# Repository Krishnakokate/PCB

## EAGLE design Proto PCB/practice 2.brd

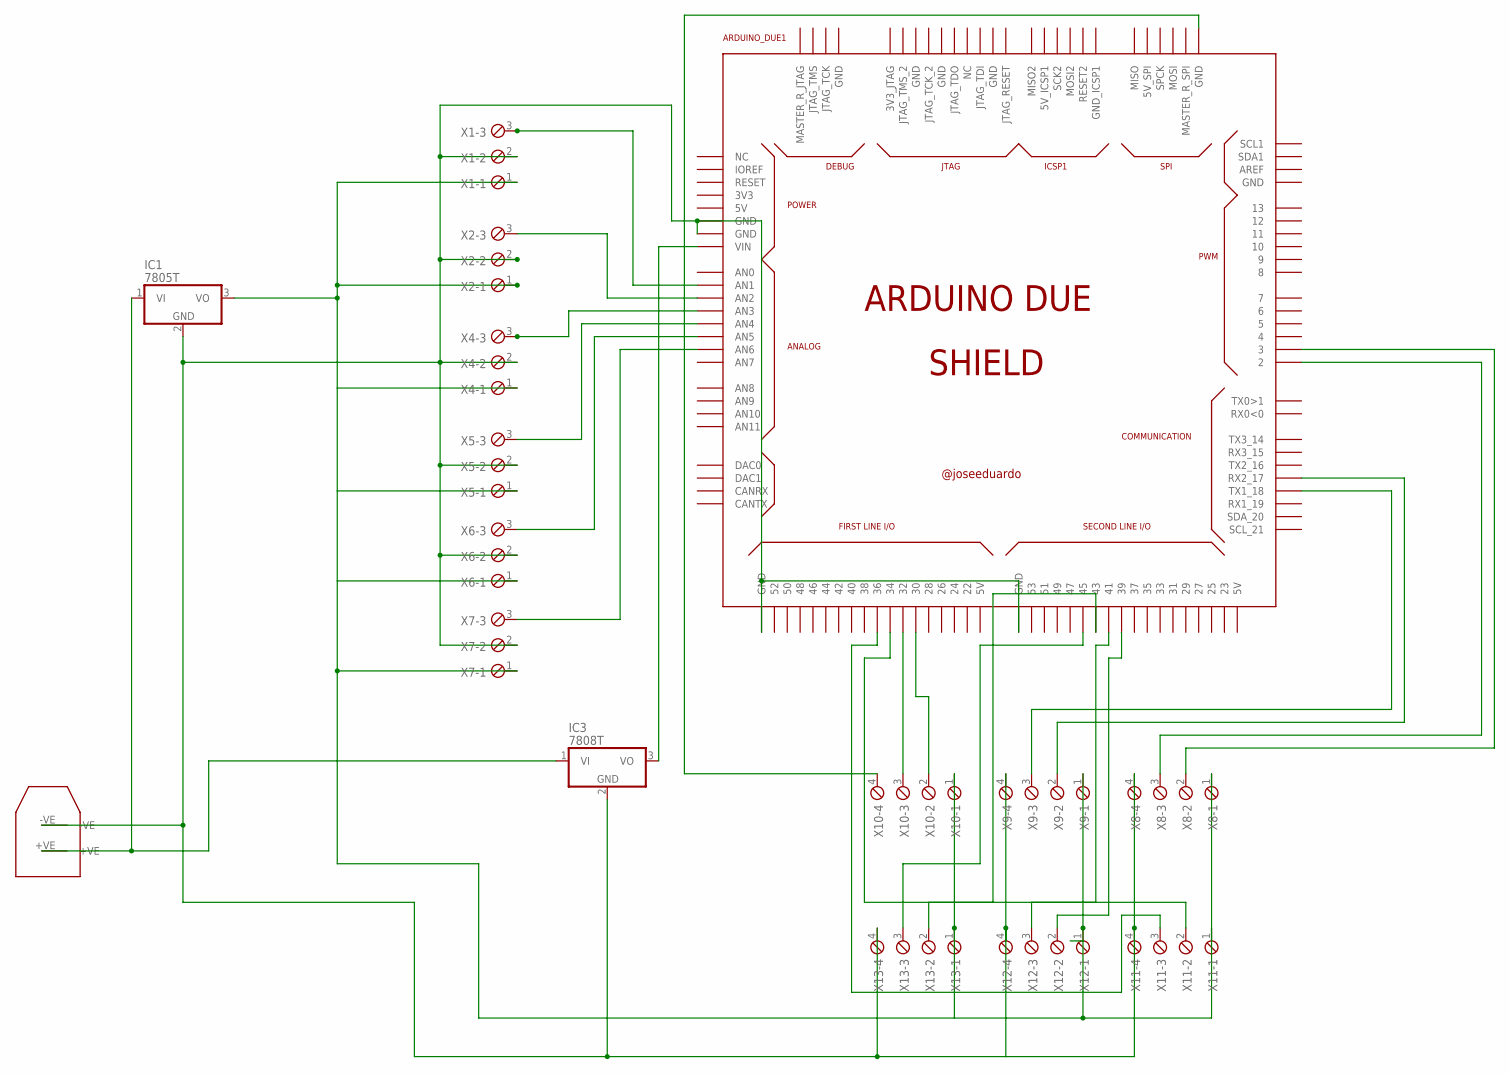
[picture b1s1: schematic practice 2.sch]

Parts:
ARDUINO_DUE1: ARDUINO_DUE_SHIELD
IC1: 7805T; TO220H
IC3: 7808T; TO220H
U$1: XT60XT60; XT60
X1, X2, X4, X5, X6, X7: MPT3; 3POL254
X8, X9, X10, X11, X12, X13: MPT4; 4POL254

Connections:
GND: ARDUINO_DUE1.GND, ARDUINO_DUE1.GND_1 (GND), ARDUINO_DUE1.GND_2 (GND), ARDUINO_DUE1.GND_3 (GND), IC1.2 (GND), IC3.2 (GND), U$1.-VE, X1.2, X2.2, X4.2, X5.2, X6.2, X7.2, X8.4, X9.4, X11.4, X12.4, X13.4
unnamed: ARDUINO_DUE1.36, X11.3
unnamed: ARDUINO_DUE1.A2 (AN2), X2.3
unnamed: ARDUINO_DUE1.A1 (AN1), X1.3
unnamed: ARDUINO_DUE1.GND_5 (GND), X10.4
unnamed: ARDUINO_DUE1.A3 (AN3), X4.3
unnamed: ARDUINO_DUE1.A4 (AN4), X5.3
unnamed: ARDUINO_DUE1.A5 (AN5), X6.3
unnamed: ARDUINO_DUE1.A6 (AN6), X7.3
unnamed: IC1.3 (VO), X1.1, X2.1, X4.1, X5.1, X6.1, X7.1, X8.1, X9.1, X10.1, X11.1, X12.1, X13.1
unnamed: ARDUINO_DUE1.30, X10.2
unnamed: ARDUINO_DUE1.32, X10.3
unnamed: IC1.1 (VI), IC3.1 (VI), U$1.+VE
unnamed: ARDUINO_DUE1.34, X11.2
unnamed: ARDUINO_DUE1.39, X12.2
unnamed: ARDUINO_DUE1.41, X12.3
unnamed: ARDUINO_DUE1.45, X13.3
unnamed: ARDUINO_DUE1.43, X13.2
unnamed: ARDUINO_DUE1.VIN, IC3.3 (VO)
unnamed: ARDUINO_DUE1.18 (TX1_18), X9.3
unnamed: ARDUINO_DUE1.17 (RX2_17), X9.2
unnamed: ARDUINO_DUE1.2, X8.3
unnamed: ARDUINO_DUE1.3, X8.2

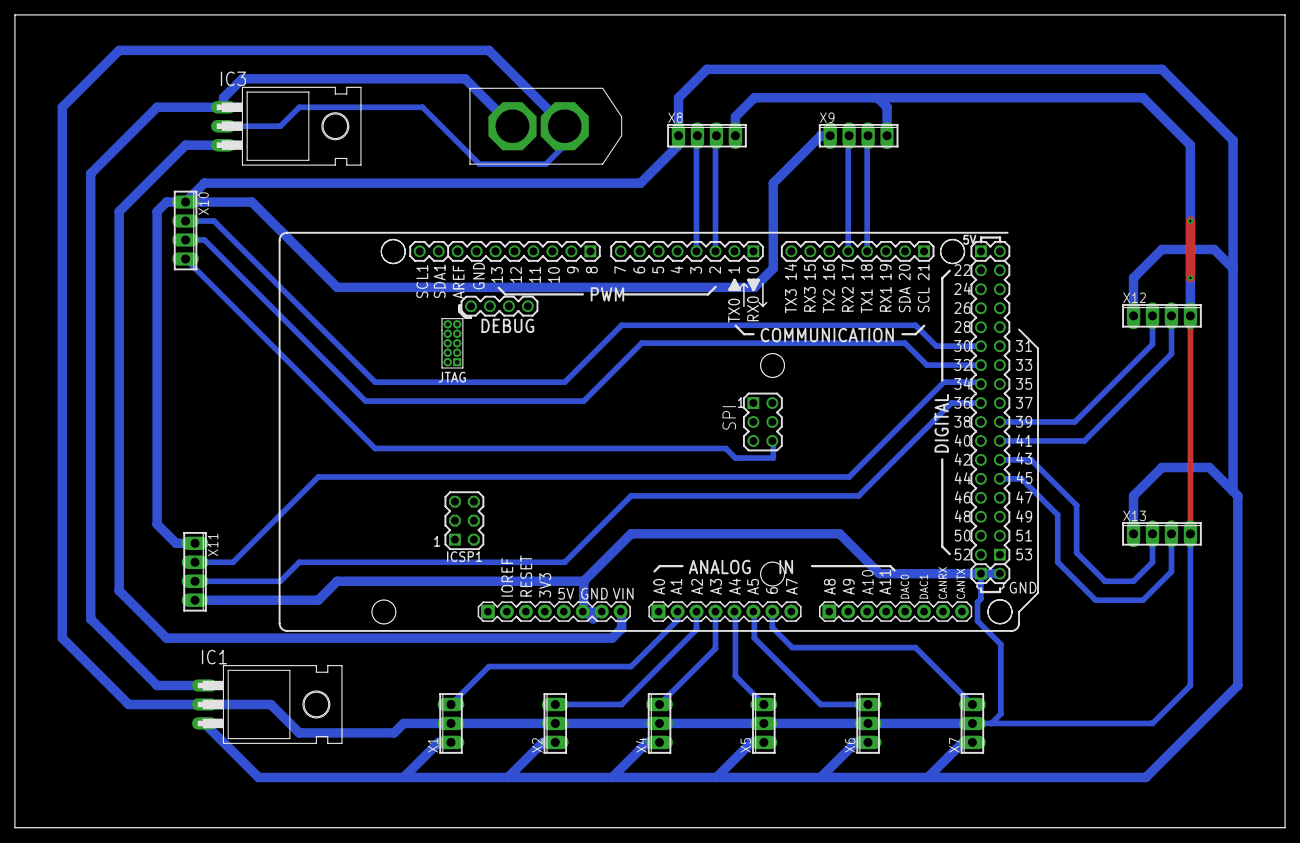
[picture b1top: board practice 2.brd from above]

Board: 2 copper layers, 170.2 x 108.9 mm, 16 parts (0 on the bottom side), 23 nets.

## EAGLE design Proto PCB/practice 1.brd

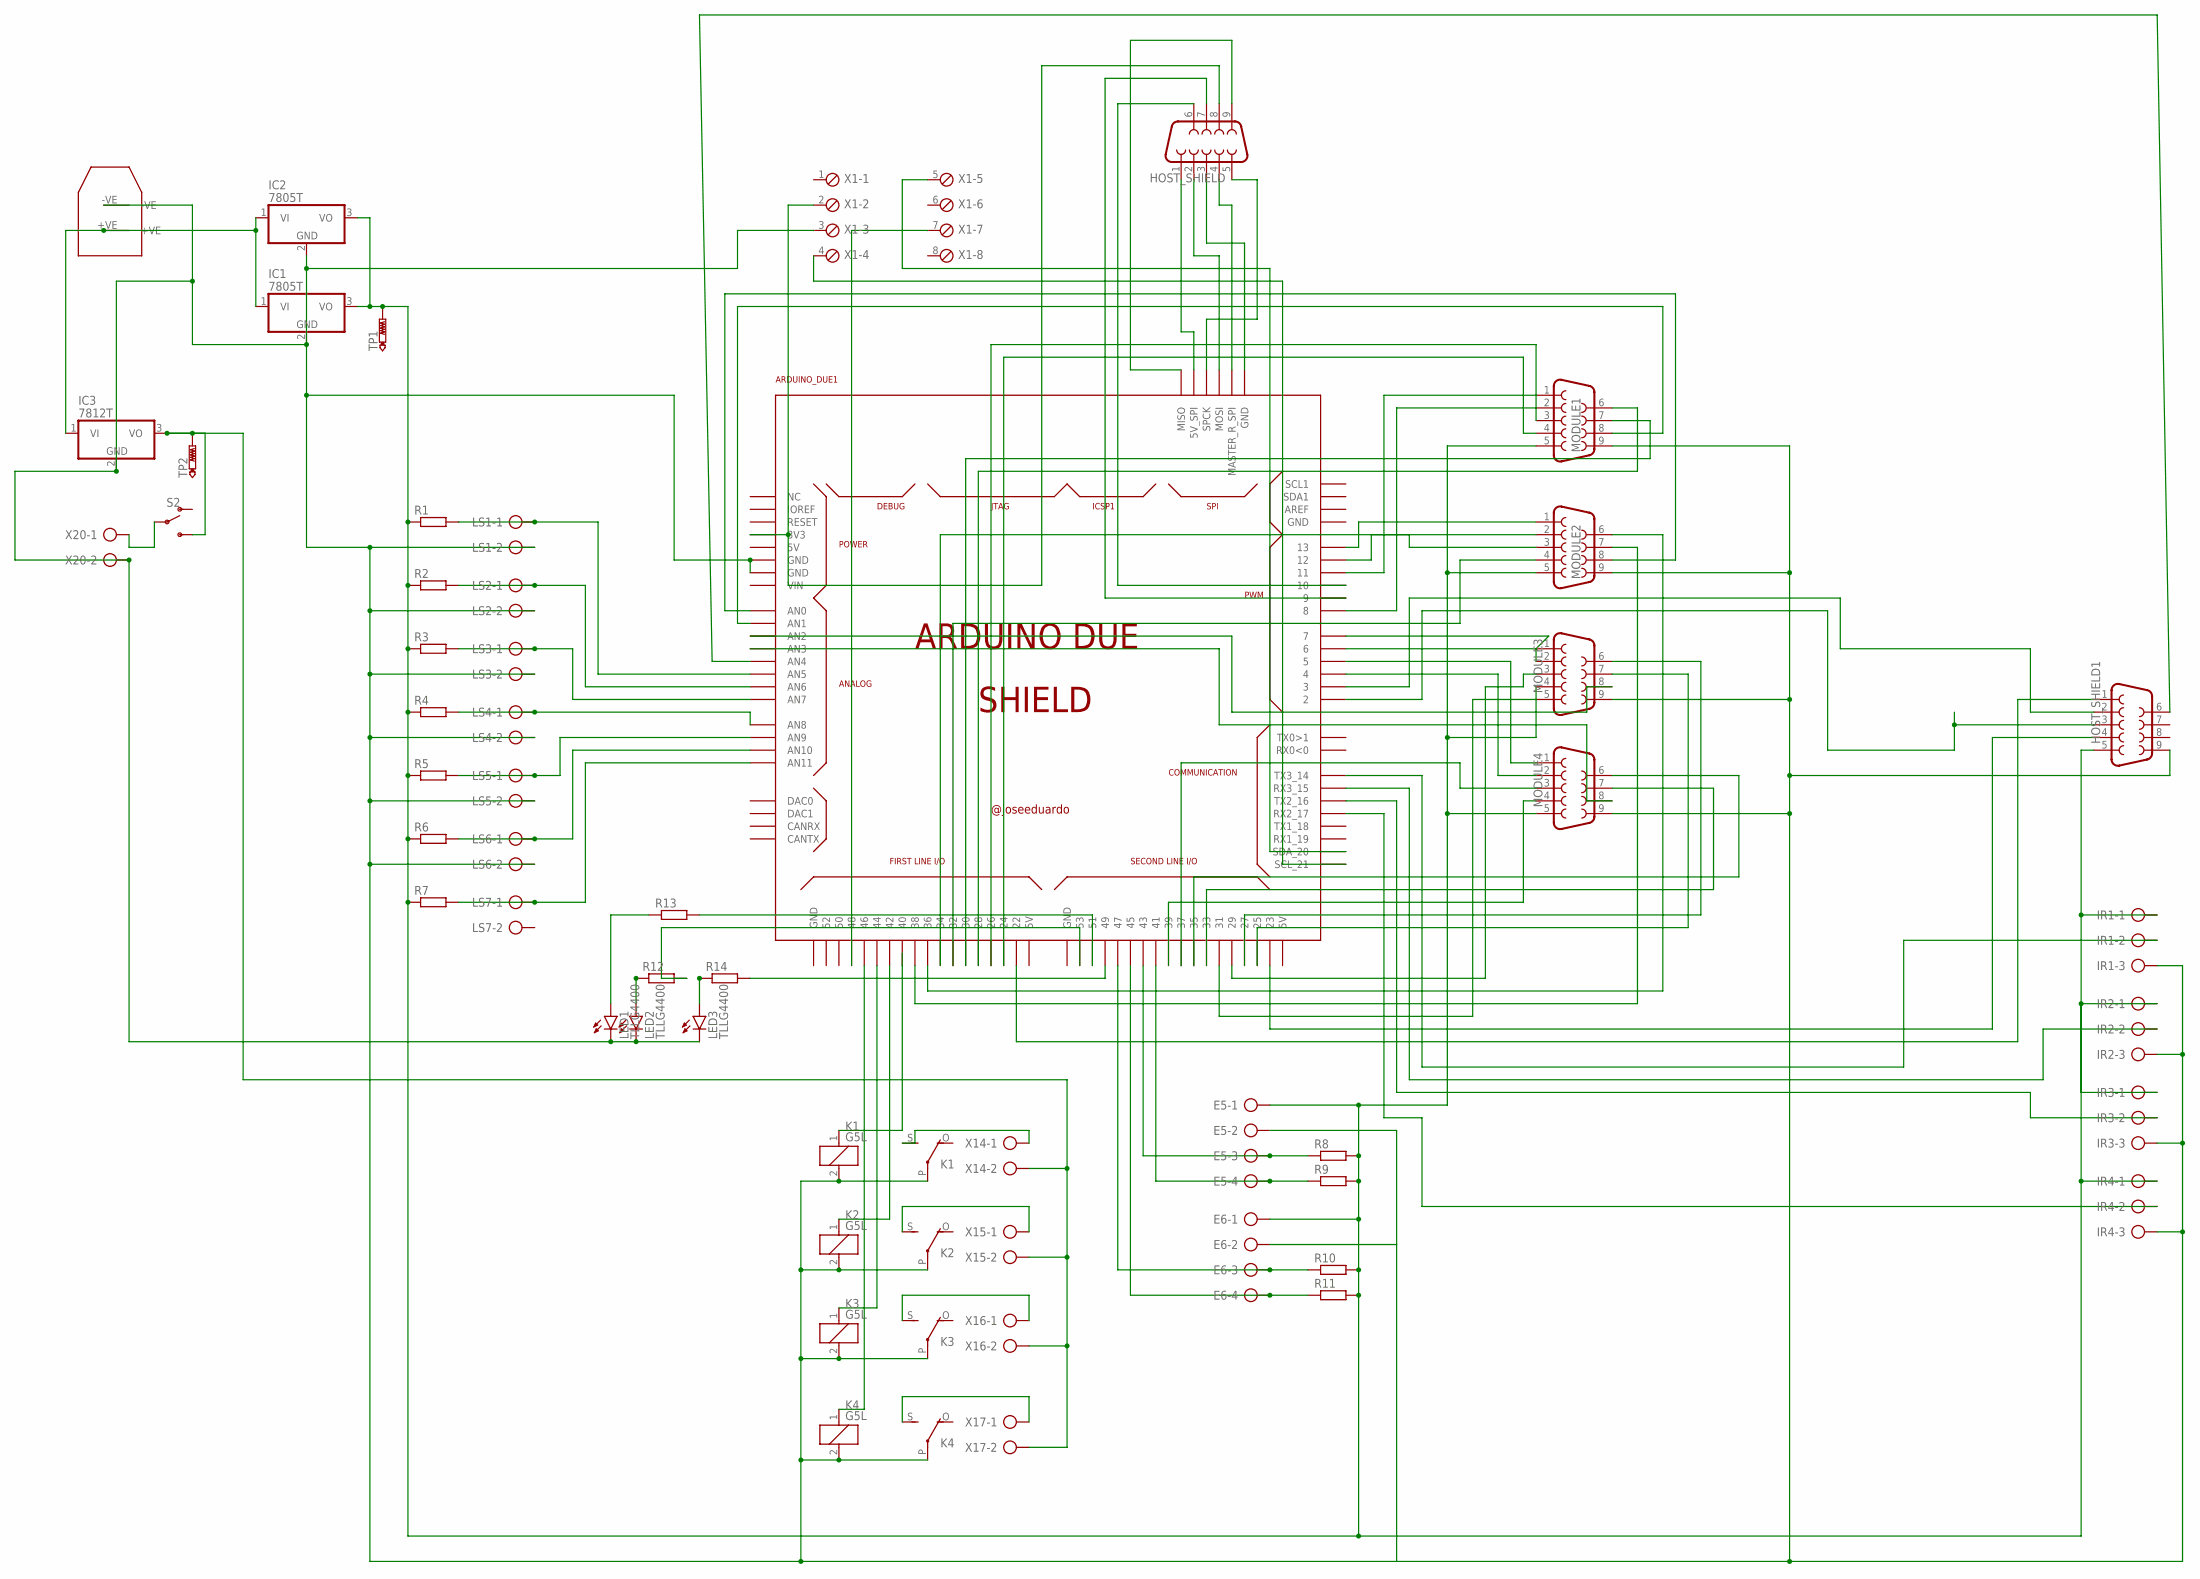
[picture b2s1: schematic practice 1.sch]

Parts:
ARDUINO_DUE1: ARDUINO_DUE_SHIELD
E5, E6: AK500/4-H
HOST_SHIELD, HOST_SHIELD1: DB9; DB9_MODULE
IC1, IC2: 7805T; TO220H
IC3: 7812T; TO220H
IR1, IR2, IR3, IR4: AK500/3-H
K1, K2, K3, K4: G5L; G5LE
LED1, LED2, LED3: TLLG4400; LED3MM
LS1, LS2, LS3, LS4, LS5, LS6, LS7: AK500/2-H
MODULE1, MODULE2, MODULE3, MODULE4: DB9; DB9_MODULE
R1, R2, R3, R4, R5, R6, R7, R8, R9, R10, R11, R12, R13, R14: R-EU_0309/10; 0309/10
S2: SWITCH-SPDT-PTH-11.6X4.0MM; SWITCH_SPDT_PTH_11.6X4.0MM
TP1, TP2: PTR1PAD1-13; P1-13
U$1: XT60XT60; XT60
X1: MPT8; 8POL254
X14, X15, X16, X17, X20: AK500/2-H

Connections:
GND: ARDUINO_DUE1.GND, ARDUINO_DUE1.GND_1 (GND), E5.2, E6.2, HOST_SHIELD1.9, IC1.2 (GND), IC2.2 (GND), IC3.2 (GND), IR1.3, IR2.3, IR3.3, IR4.3, K1.2, K1.P, K2.2, K2.P, K3.2, K3.P, K4.2, K4.P, LED1.K (C), LED2.K (C), LED3.K (C), LS1.2, LS2.2, LS3.2, LS4.2, LS5.2, LS6.2, MODULE1.9, MODULE2.9, MODULE3.9, MODULE4.9, U$1.-VE, X1.3, X20.2
unnamed: ARDUINO_DUE1.35, MODULE4.6
unnamed: ARDUINO_DUE1.37, MODULE4.3
unnamed: ARDUINO_DUE1.39, MODULE4.4
unnamed: ARDUINO_DUE1.A5 (AN5), LS1.1, R1.2
unnamed: ARDUINO_DUE1.A6 (AN6), LS2.1, R2.2
unnamed: ARDUINO_DUE1.A7 (AN7), LS3.1, R3.2
unnamed: ARDUINO_DUE1.A8 (AN8), LS4.1, R4.2
unnamed: ARDUINO_DUE1.A9 (AN9), LS5.1, R5.2
unnamed: ARDUINO_DUE1.A10 (AN10), LS6.1, R6.2
unnamed: ARDUINO_DUE1.A11 (AN11), LS7.1, R7.2
unnamed: ARDUINO_DUE1.3, HOST_SHIELD1.2
unnamed: ARDUINO_DUE1.43, E5.3, R8.1
unnamed: ARDUINO_DUE1.A4 (AN4), HOST_SHIELD1.6
unnamed: ARDUINO_DUE1.40, K1.1
unnamed: ARDUINO_DUE1.41, E5.4, R9.1
unnamed: ARDUINO_DUE1.47, E6.3, R10.1
unnamed: ARDUINO_DUE1.45, E6.4, R11.1
unnamed: ARDUINO_DUE1.53, R12.2
unnamed: IC1.1 (VI), IC2.1 (VI), IC3.1 (VI), U$1.+VE
unnamed: ARDUINO_DUE1.42, K2.1
unnamed: ARDUINO_DUE1.44, K3.1
unnamed: ARDUINO_DUE1.46, K4.1
unnamed: ARDUINO_DUE1.2, HOST_SHIELD1.3
unnamed: ARDUINO_DUE1.22, HOST_SHIELD1.1
unnamed: ARDUINO_DUE1.23, HOST_SHIELD1.4
unnamed: IC3.3 (VO), S2.3 (S), TP2.TP, X14.2, X15.2, X16.2, X17.2
unnamed: K1.S, X14.1
unnamed: K2.S, X15.1
unnamed: K3.S, X16.1
unnamed: K4.S, X17.1
unnamed: S2.2, X20.1
unnamed: ARDUINO_DUE1.14 (TX3_14), IR1.2
unnamed: ARDUINO_DUE1.15 (RX3_15), IR2.2
unnamed: ARDUINO_DUE1.16 (TX2_16), IR3.2
unnamed: ARDUINO_DUE1.17 (RX2_17), IR4.2
unnamed: ARDUINO_DUE1.3V3, HOST_SHIELD.8, X1.2
unnamed: ARDUINO_DUE1.21 (SCL_21), X1.4
unnamed: ARDUINO_DUE1.20 (SDA_20), X1.5
unnamed: ARDUINO_DUE1.48, X1.7
unnamed: ARDUINO_DUE1.5V_2 (5V_SPI), HOST_SHIELD.1
unnamed: ARDUINO_DUE1.MOSI, HOST_SHIELD.2
unnamed: ARDUINO_DUE1.GND_5 (GND), HOST_SHIELD.3
unnamed: ARDUINO_DUE1.11, MODULE1.1
unnamed: ARDUINO_DUE1.8, MODULE1.2
unnamed: ARDUINO_DUE1.26, MODULE1.3
unnamed: ARDUINO_DUE1.24, MODULE1.4
unnamed: ARDUINO_DUE1.28, MODULE1.6
unnamed: ARDUINO_DUE1.30, MODULE1.7
unnamed: ARDUINO_DUE1.13, MODULE2.1
unnamed: ARDUINO_DUE1.12, MODULE2.2
unnamed: ARDUINO_DUE1.34, MODULE2.3
unnamed: ARDUINO_DUE1.36, MODULE2.6
unnamed: ARDUINO_DUE1.32, MODULE2.4
unnamed: ARDUINO_DUE1.38, MODULE2.7
unnamed: ARDUINO_DUE1.A1 (AN1), MODULE1.8
unnamed: ARDUINO_DUE1.A0 (AN0), MODULE2.8
unnamed: ARDUINO_DUE1.A2 (AN2), MODULE3.8
unnamed: ARDUINO_DUE1.A3 (AN3), MODULE4.8
unnamed: ARDUINO_DUE1.7, MODULE3.1
unnamed: ARDUINO_DUE1.6, MODULE3.2
unnamed: ARDUINO_DUE1.5, MODULE4.1
unnamed: ARDUINO_DUE1.4, MODULE4.2
unnamed: ARDUINO_DUE1.29, MODULE3.3
unnamed: ARDUINO_DUE1.31, E5.1, E6.1, HOST_SHIELD1.5, IC1.3 (VO), IC2.3 (VO), IR1.1, IR2.1, IR3.1, IR4.1, MODULE1.5, MODULE2.5, MODULE3.4, MODULE3.5, MODULE4.5, R1.1, R2.1, R3.1, R4.1, R5.1, R6.1, R7.1, R8.2, R9.2, R10.2, R11.2, TP1.TP
unnamed: ARDUINO_DUE1.25, MODULE3.7
unnamed: ARDUINO_DUE1.27, MODULE3.6
unnamed: ARDUINO_DUE1.33, MODULE4.7
unnamed: ARDUINO_DUE1.MISO, HOST_SHIELD.9
unnamed: ARDUINO_DUE1.MASTER_RESET_SPI (MASTER_R_SPI), HOST_SHIELD.4
unnamed: ARDUINO_DUE1.SPCK, HOST_SHIELD.5
unnamed: ARDUINO_DUE1.49, R14.2
unnamed: ARDUINO_DUE1.51, R13.2
unnamed: LED2.A, R12.1
unnamed: ARDUINO_DUE1.9, HOST_SHIELD.7
unnamed: ARDUINO_DUE1.10, HOST_SHIELD.6
unnamed: LED1.A, R13.1
unnamed: LED3.A, R14.1

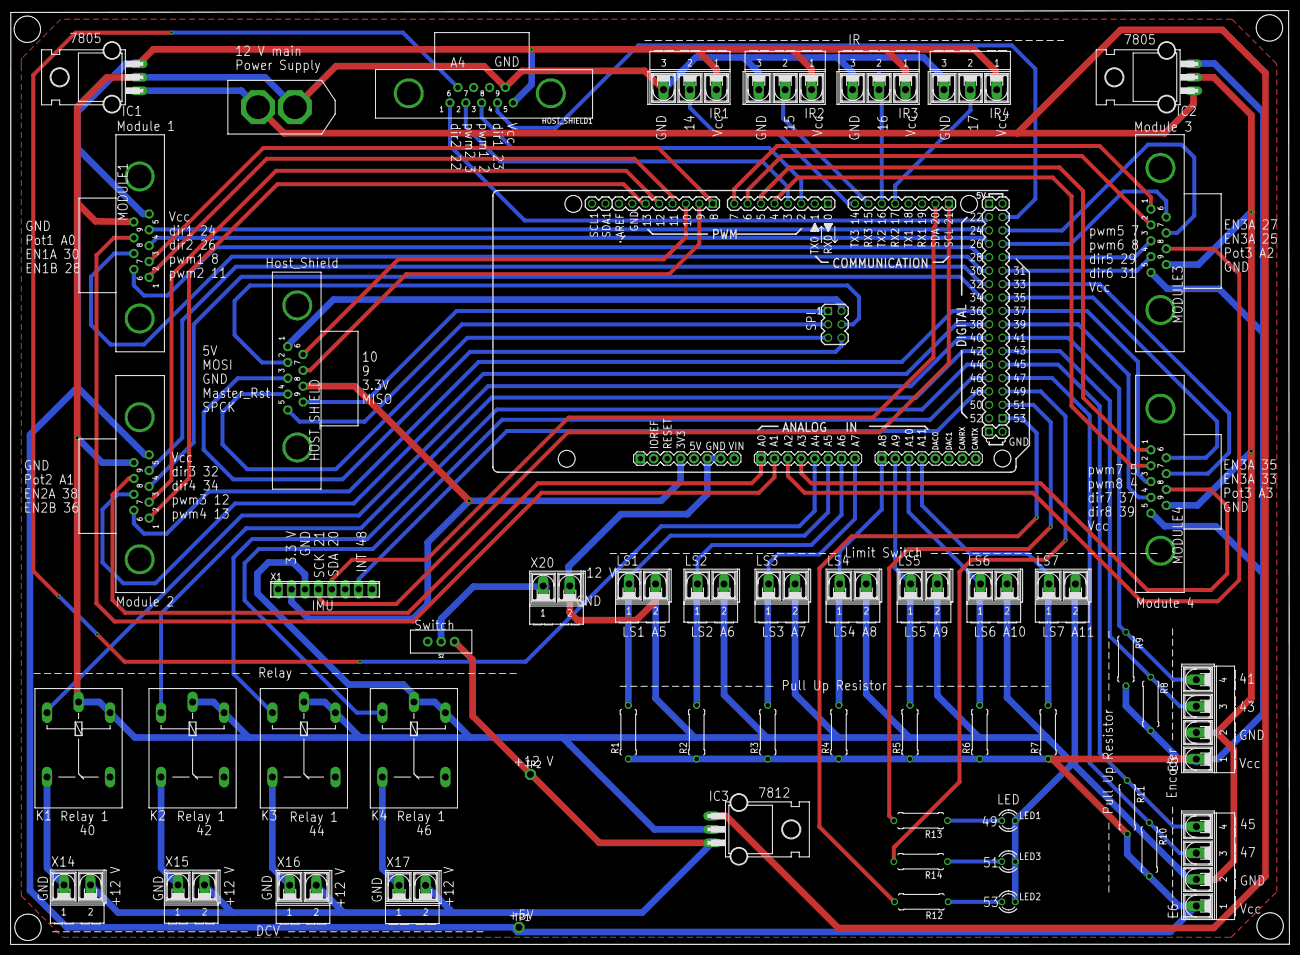
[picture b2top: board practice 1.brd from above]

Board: 2 copper layers, 242.2 x 176.8 mm, 54 parts (0 on the bottom side), 78 nets.

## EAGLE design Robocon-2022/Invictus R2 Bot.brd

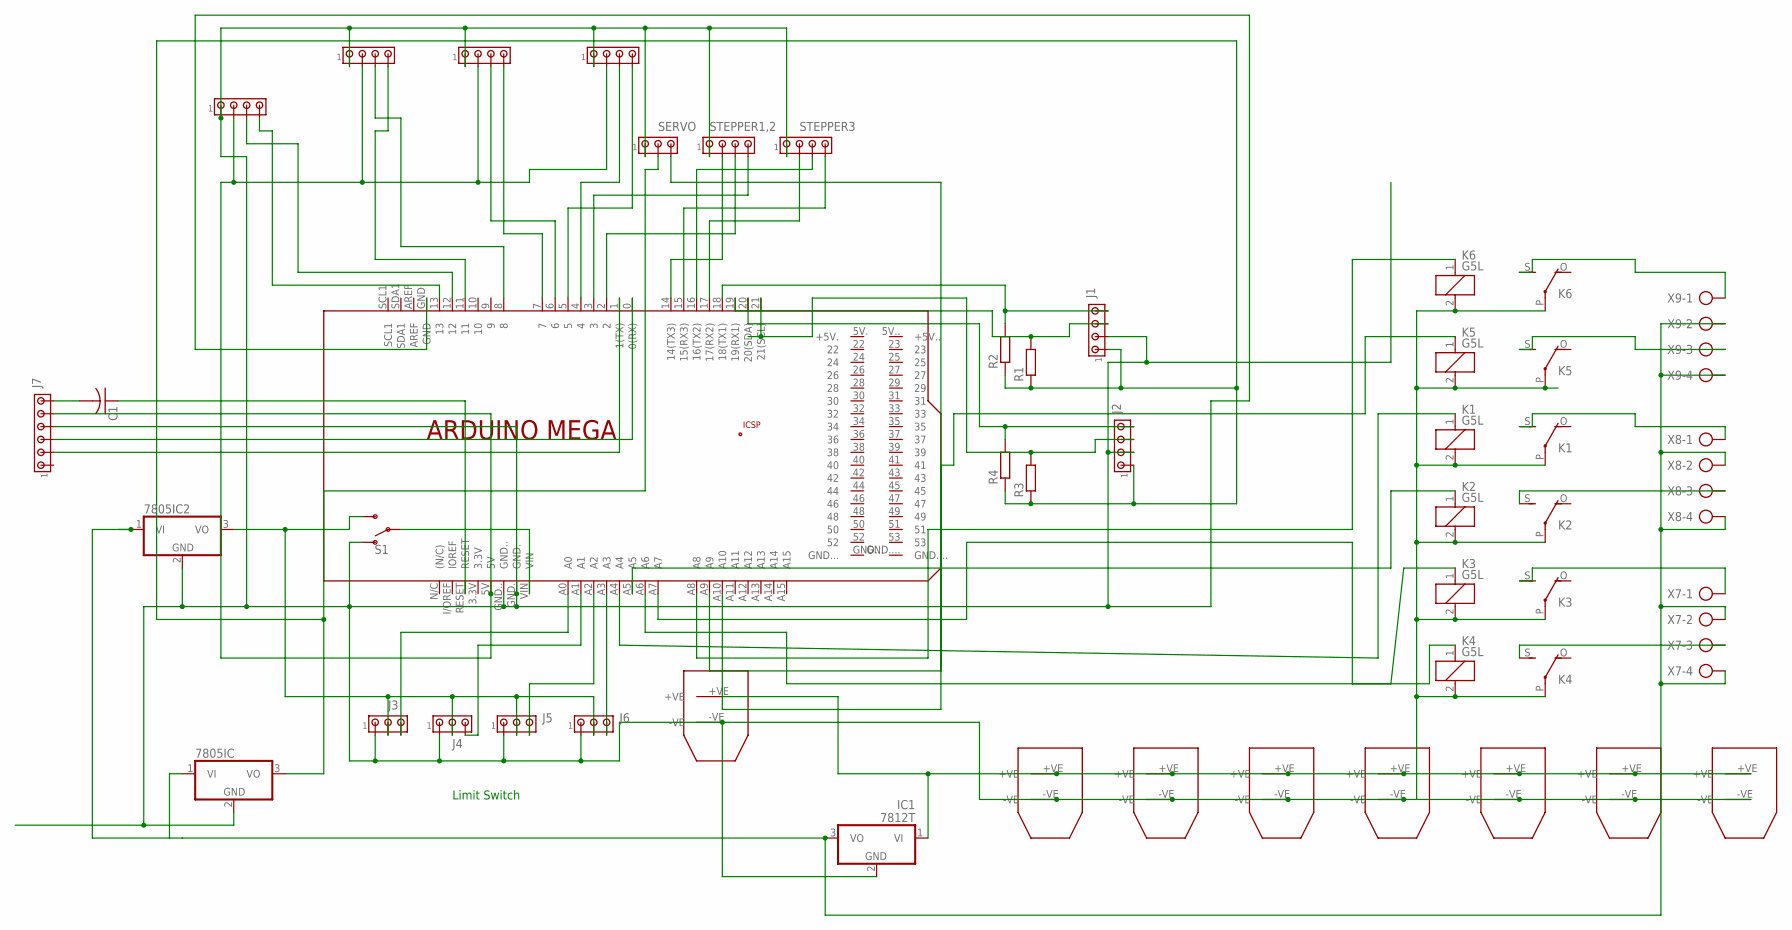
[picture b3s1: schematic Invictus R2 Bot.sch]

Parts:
7805IC: 7812T; TO220H
7805IC2: 7805T; TO220H
C1: C-US025-030X050; C025-030X050
IC1: 7812T; TO220H
J1, J2: MTA04-100; 10X04MTA
J3, J4, J5, J6: MTA03-100; 10X03MTA
J7: MTA06-100; 10X06MTA
K1, K2, K3, K4, K5, K6: G5L; G5LE
PCB2: ARDUINO_MEGA2560
R1, R2, R3, R4: R-EU_0207/7; 0207/7
S1: SWITCH-SPDT-PTH-11.6X4.0MM; SWITCH_SPDT_PTH_11.6X4.0MM
SERVO: MTA03-100; 10X03MTA
STEPPER1,1, STEPPER1,2, STEPPER1,3, STEPPER1,4, STEPPER1,5, STEPPER3: MTA04-100; 10X04MTA
X7, X8, X9: AK500/4-H
XT1, XT2, XT3, XT4, XT5, XT6, XT7, XT60: XT60XT60; XT60

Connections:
5V: 7805IC.3 (VO), J1.1, J2.1, R1.1, R2.1, R3.1, R4.1, SERVO.2
12V: 7805IC.1 (VI), 7805IC2.1 (VI), IC1.3 (VO), X7.2, X7.4, X8.2, X8.4, X9.2, X9.4
GND: 7805IC.2 (GND), 7805IC2.2 (GND), IC1.2 (GND), J1.2, J2.2, J3.1, J4.1, J5.1, J6.1, J7.4, K1.2, K1.P, K2.2, K2.P, K3.2, K3.P, K4.2, K4.P, K5.2, K5.P, K6.2, K6.P, PCB2.GND, PCB2.GND., PCB2.GND.., S1.1 (O), SERVO.1, STEPPER1,1.1, STEPPER1,2.1, STEPPER1,3.1, STEPPER1,4.1, STEPPER1,5.1, STEPPER3.1, XT1.-VE, XT2.-VE, XT3.-VE, XT4.-VE, XT5.-VE, XT6.-VE, XT7.-VE, XT60.-VE
unnamed: PCB2.VIN, S1.2
unnamed: K4.1, PCB2.A7
unnamed: PCB2.5, STEPPER1,5.4
unnamed: K3.1, PCB2.A6
unnamed: PCB2.3, STEPPER1,2.4
unnamed: J2.4, PCB2.20 (20(SDA)), R4.2
unnamed: J2.3, PCB2.21 (21(SCL)), R3.2
unnamed: J1.3, PCB2.19 (19(RX1)), R1.2
unnamed: PCB2.4, STEPPER1,5.3
unnamed: PCB2.6, STEPPER1,4.3
unnamed: PCB2.13, STEPPER1,1.4
unnamed: PCB2.12, STEPPER1,1.3
unnamed: PCB2.11, STEPPER1,3.4
unnamed: PCB2.8, STEPPER1,3.3
unnamed: PCB2.7, STEPPER1,4.4
unnamed: PCB2.17 (17(RX2)), STEPPER3.2
unnamed: J1.4, PCB2.18 (18(TX1)), R2.2
unnamed: K2.1, PCB2.A5
unnamed: PCB2.16 (16(TX2)), STEPPER3.3
unnamed: K1.1, PCB2.A4
unnamed: J7.3, PCB2.0 (0(RX))
unnamed: K6.1, PCB2.A8
unnamed: PCB2.A10, SERVO.3
unnamed: J6.3, PCB2.A3
unnamed: J7.2, PCB2.1 (1(TX))
unnamed: PCB2.2, STEPPER1,2.3
unnamed: PCB2.14 (14(TX3)), STEPPER1,2.2
unnamed: PCB2.15 (15(RX3)), STEPPER3.4
unnamed: J3.3, PCB2.A0
unnamed: J4.3, PCB2.A1
unnamed: J5.3, PCB2.A2
unnamed: K5.1, PCB2.A9
unnamed: C1.1, PCB2.RESET
unnamed: 7805IC2.3 (VO), J3.2, J4.2, J5.2, J6.2, S1.3 (S)
unnamed: K6.S, X9.1
unnamed: K5.S, X9.3
unnamed: K1.S, X8.1
unnamed: K2.S, X8.3
unnamed: K3.S, X7.1
unnamed: C1.2, J7.6
unnamed: K4.S, X7.3
unnamed: J7.5, PCB2.5V, STEPPER1,1.2, STEPPER1,3.2, STEPPER1,4.2, STEPPER1,5.2
VCC: IC1.1 (VI), XT1.+VE, XT2.+VE, XT3.+VE, XT4.+VE, XT5.+VE, XT6.+VE, XT7.+VE, XT60.+VE

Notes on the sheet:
Limit Switch

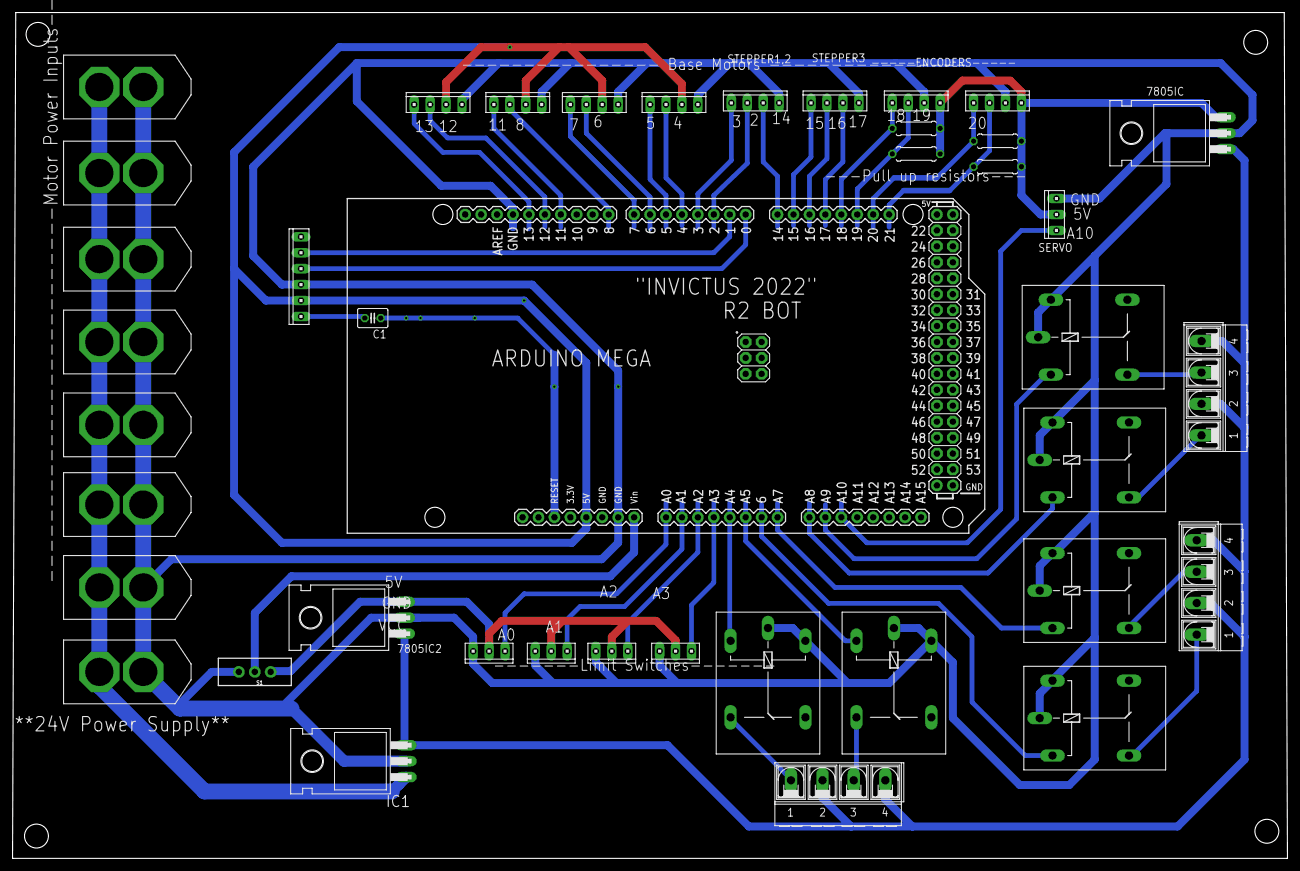
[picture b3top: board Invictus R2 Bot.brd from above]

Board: 2 copper layers, 203.2 x 134.8 mm, 41 parts (0 on the bottom side), 46 nets.

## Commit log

2024-01-17 Create mnbvc

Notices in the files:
parts and their libraries:
SparkFun-Switches: Licensing: Creative Commons ShareAlike 4.0 International - https://creativecommons.org/licenses/by-sa/4.0
